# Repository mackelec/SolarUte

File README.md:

# SolarUte

The story about converting a 2000 4WD Ford Couier Diesel Ute (Mazda B2500) to Battery Electric.

## [The Story](https://github.com/mackelec/SolarUte/blob/master/The_Story/readme.md)

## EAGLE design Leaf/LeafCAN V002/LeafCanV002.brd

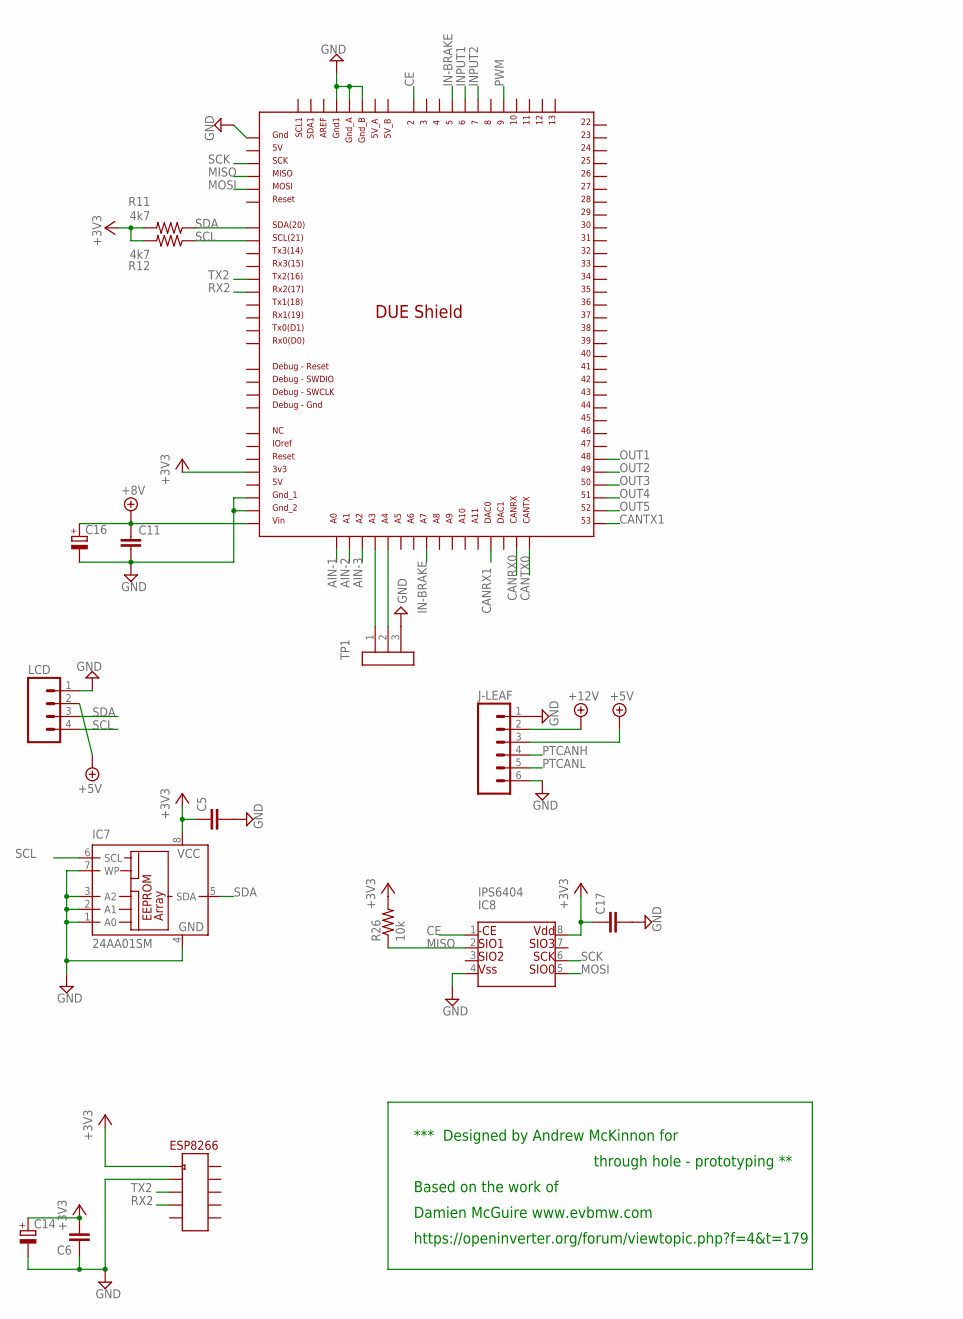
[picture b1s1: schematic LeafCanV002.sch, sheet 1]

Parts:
C5, C6, C11, C17: BCAP
C14, C16: C-RB200100; CPOL-RADIAL-10UF-25V
ESP8266: IDC10; IDC10-SMALL
IC1: DUE(NORMAL)
IC7: 24AA01SM; SO-08M
IC8: IPS6404; SO-08
J-LEAF: MO6POL; MOLEX-6
LCD: MO4POL; MOLEX-4
R11, R12: 4k7; AXIAL-0.4
R26: 10k; R1206
TP1: SIL3

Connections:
+3V3: C5.1, C6.2, C14.1 (+), C17.1, ESP8266.1, IC1.3V3, IC7.8 (VCC), IC8.8, R11.P$2 (2), R12.P$2 (2), R26.2; also elsewhere on the board
+5V: J-LEAF.3, LCD.2; also elsewhere on the board
+8V: C11.1, C16.1 (+), IC1.VIN; also elsewhere on the board
+12V: J-LEAF.2; also elsewhere on the board
AIN-1: IC1.A0; also elsewhere on the board
AIN-2: IC1.A1; also elsewhere on the board
AIN-3: IC1.A2; also elsewhere on the board
CANRX0: IC1.CANRX; also elsewhere on the board
CANRX1: IC1.DAC0; also elsewhere on the board
CANTX0: IC1.CANTX; also elsewhere on the board
CANTX1: IC1.53; also elsewhere on the board
CE: IC1.2, IC8.1
GND: C5.2, C6.1, C11.2, C14.2 (-), C16.2 (-), C17.2, ESP8266.3, IC1.5V_ICSP, IC1.GND1, IC1.GND_1, IC1.GND_2, IC1.GND_A, IC1.GND_B, IC7.1 (A0), IC7.2 (A1), IC7.3 (A2), IC7.4 (GND), IC7.7 (WP), IC8.4, J-LEAF.1, J-LEAF.6, LCD.1, TP1.3; also elsewhere on the board
IN-BRAKE: IC1.5, IC1.A7; also elsewhere on the board
INPUT1: IC1.6; also elsewhere on the board
INPUT2: IC1.7; also elsewhere on the board
MISO: IC1.MISO_ICSP, IC8.2, R26.1
MOSI: IC1.MOSI_ICSP, IC8.5
unnamed: IC1.A3, TP1.1
unnamed: IC1.A4, TP1.2
OUT1: IC1.48; also elsewhere on the board
OUT2: IC1.49; also elsewhere on the board
OUT3: IC1.50; also elsewhere on the board
OUT4: IC1.51; also elsewhere on the board
OUT5: IC1.52; also elsewhere on the board
PTCANH: J-LEAF.4; also elsewhere on the board
PTCANL: J-LEAF.5; also elsewhere on the board
PWM: IC1.9; also elsewhere on the board
RX2: ESP8266.7, IC1.RX2
SCK: IC1.SCK_ICSP, IC8.6
SCL: IC1.SCL, IC7.6 (SCL), LCD.4, R12.P$1 (1)
SDA: IC1.SDA, IC7.5 (SDA), LCD.3, R11.P$1 (1)
TX2: ESP8266.5, IC1.TX2

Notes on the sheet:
Based on the work of
Damien McGuire www.evbmw.com
https://openinverter.org/forum/viewtopic.php?f=4&t=179
*** Designed by Andrew McKinnon for
through hole - prototyping **

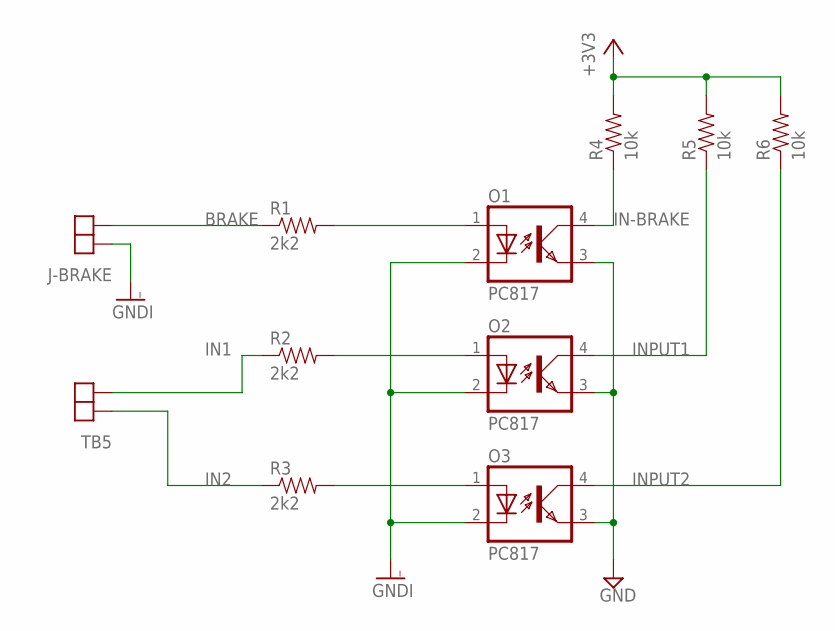
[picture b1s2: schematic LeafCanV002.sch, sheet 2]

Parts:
J-BRAKE: TB2381; TB-KF2EDG381-2P
O1, O2, O3: PC817; DIL04
R1, R2, R3: 2k2; AXIAL-0.4
R4, R5, R6: 10k; AXIAL-0.4
TB5: TB2381; TB-KF2EDG381-2P

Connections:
+3V3: R4.P$2 (2), R5.P$2 (2), R6.P$2 (2); also elsewhere on the board
BRAKE: J-BRAKE.1, R1.P$1 (1)
GND: O1.3 (EMIT), O2.3 (EMIT), O3.3 (EMIT); also elsewhere on the board
GNDI: J-BRAKE.2, O1.2 (C), O2.2 (C), O3.2 (C); also elsewhere on the board
IN1: R2.P$1 (1), TB5.1
IN2: R3.P$1 (1), TB5.2
IN-BRAKE: O1.4 (COL), R4.P$1 (1); also elsewhere on the board
INPUT1: O2.4 (COL), R5.P$1 (1); also elsewhere on the board
INPUT2: O3.4 (COL), R6.P$1 (1); also elsewhere on the board
unnamed: O3.1 (A), R3.P$2 (2)
unnamed: O2.1 (A), R2.P$2 (2)
unnamed: O1.1 (A), R1.P$2 (2)

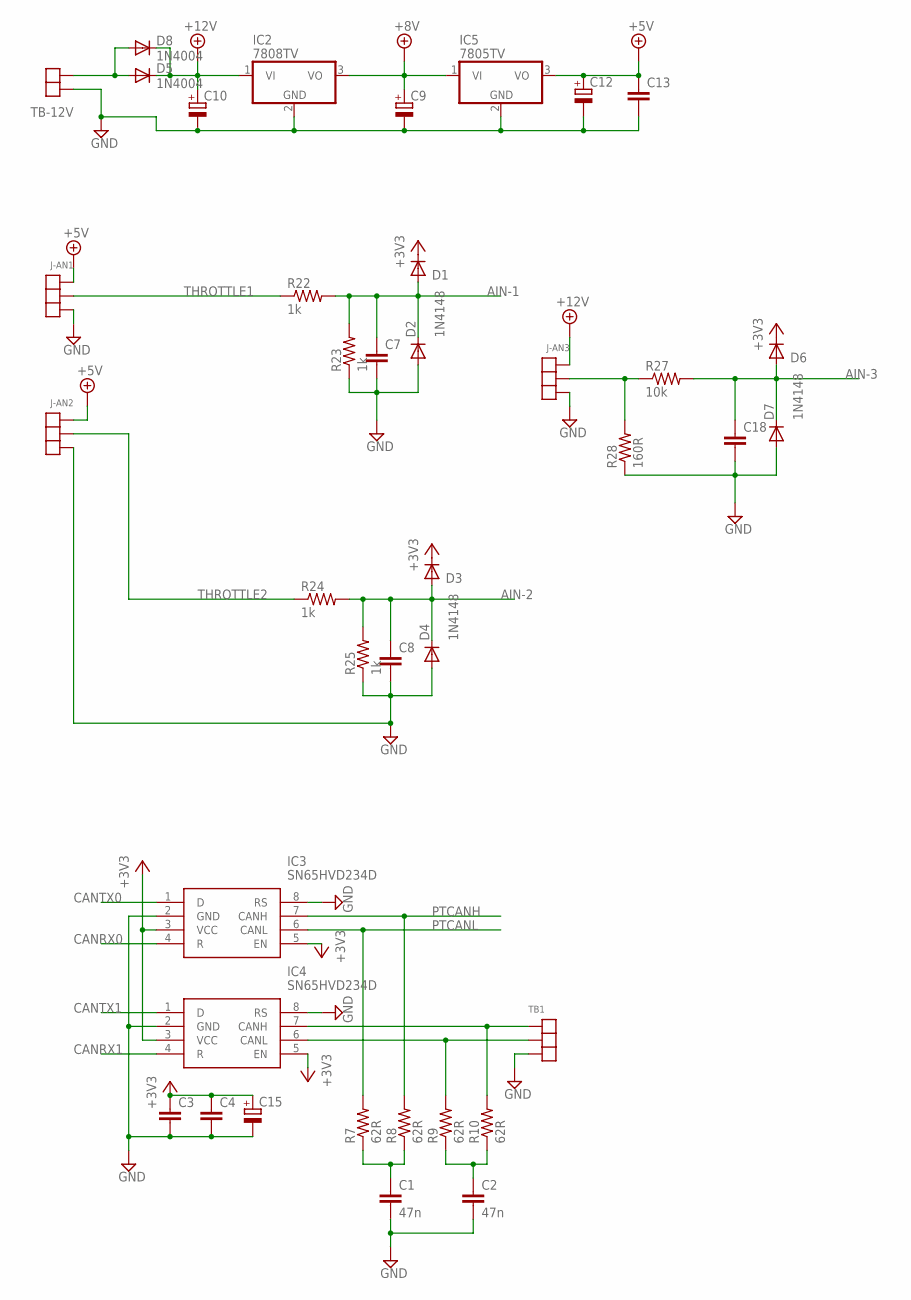
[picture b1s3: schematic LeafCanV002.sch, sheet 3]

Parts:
C1, C2: 47n; C025-030X050
C3, C4, C7, C8, C13, C18: BCAP
C9, C12, C15: C-RB200100; CPOL-RADIAL-10UF-25V
C10: CPOL-EUE7.5-18; E7,5-18
D1, D2, D3, D4, D6, D7: 1N4148; D3
D5, D8: 1N4004; DO41-10
IC2: 7808TV; TO220V
IC3, IC4: SN65HVD234D; SOIC127P600X175-8N
IC5: 7805TV; TO220V
J-AN1, J-AN2, J-AN3: TB3381V; TB-KF2EDG381-3-V
R7, R8, R9, R10: 62R; AXIAL-0.4
R22, R23, R24, R25: 1k; AXIAL-0.4
R27: 10k; AXIAL-0.4
R28: 160R; AXIAL-0.4
TB1: TB3381V; TB-KF2EDG381-3-V
TB-12V: TB2381; TB-KF2EDG381-2P

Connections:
+3V3: C3.1, C4.1, C15.1 (+), D1.C, D3.C, D6.C, IC3.3 (VCC), IC3.5 (EN), IC4.3 (VCC), IC4.5 (EN); also elsewhere on the board
+5V: C12.1 (+), C13.1, IC5.3 (VO), J-AN1.1, J-AN2.1; also elsewhere on the board
+8V: C9.1 (+), IC2.3 (VO), IC5.1 (VI); also elsewhere on the board
+12V: C10.+, D5.C, D8.C, IC2.1 (VI), J-AN3.1; also elsewhere on the board
AIN-1: C7.1, D1.A, D2.C, R22.P$2 (2), R23.P$2 (2); also elsewhere on the board
AIN-2: C8.1, D3.A, D4.C, R24.P$2 (2), R25.P$2 (2); also elsewhere on the board
AIN-3: C18.1, D6.A, D7.C, R27.P$2 (2); also elsewhere on the board
CANRX0: IC3.4 (R); also elsewhere on the board
CANRX1: IC4.4 (R); also elsewhere on the board
CANTX0: IC3.1 (D); also elsewhere on the board
CANTX1: IC4.1 (D); also elsewhere on the board
GND: C1.2, C2.2, C3.2, C4.2, C7.2, C8.2, C9.2 (-), C10.-, C12.2 (-), C13.2, C15.2 (-), C18.2, D2.A, D4.A, D7.A, IC2.2 (GND), IC3.2 (GND), IC3.8 (RS), IC4.2 (GND), IC4.8 (RS), IC5.2 (GND), J-AN1.3, J-AN2.3, J-AN3.3, R23.P$1 (1), R25.P$1 (1), R28.P$1 (1), TB1.3, TB-12V.2; also elsewhere on the board
unnamed: C1.1, R7.P$1 (1), R8.P$1 (1)
unnamed: C2.1, R9.P$1 (1), R10.P$1 (1)
unnamed: J-AN3.2, R27.P$1 (1), R28.P$2 (2)
unnamed: IC4.7 (CANH), R10.P$2 (2), TB1.1
unnamed: IC4.6 (CANL), R9.P$2 (2), TB1.2
unnamed: D5.A, D8.A, TB-12V.1
PTCANH: IC3.7 (CANH), R8.P$2 (2); also elsewhere on the board
PTCANL: IC3.6 (CANL), R7.P$2 (2); also elsewhere on the board
THROTTLE1: J-AN1.2, R22.P$1 (1)
THROTTLE2: J-AN2.2, R24.P$1 (1)

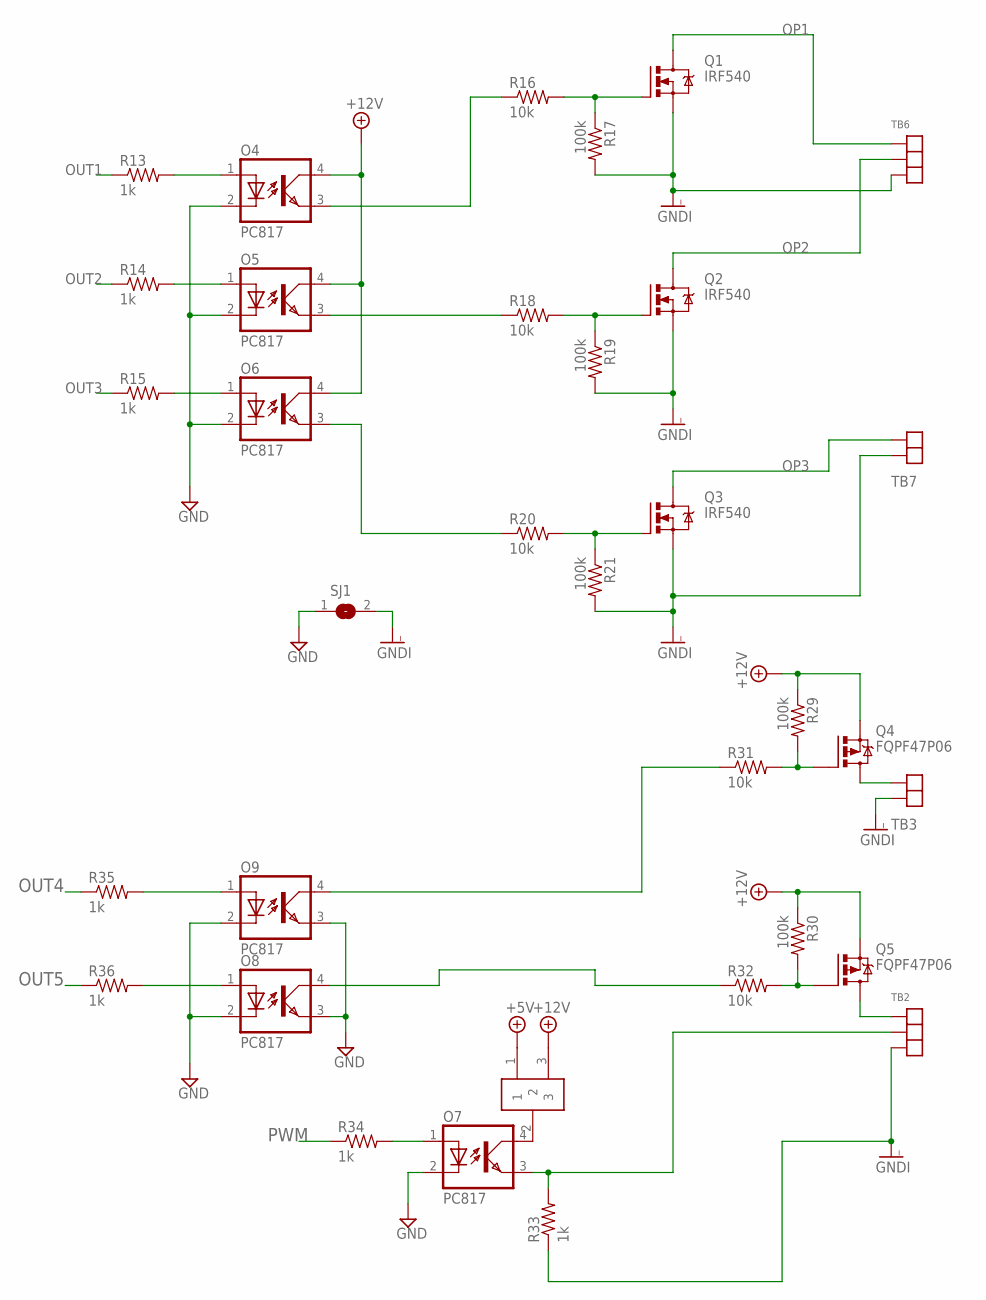
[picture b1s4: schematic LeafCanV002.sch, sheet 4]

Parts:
JP1: JP1X3
O4, O5, O6, O7: PC817; DIL04
O8, O9: PC817; DIL04; MPN PC817X4J000F
Q1, Q2, Q3: IRF540; TO220BV
Q4, Q5: FQPF47P06; TO220BV
R13, R14, R15, R33, R34, R35, R36: 1k; AXIAL-0.4
R16, R18, R20, R31, R32: 10k; AXIAL-0.4
R17, R19, R21, R29, R30: 100k; AXIAL-0.4
SJ1: SJ
TB2, TB6: TB3381; TB-KF2EDG381-3P
TB3, TB7: TB2381; TB-KF2EDG381-2P

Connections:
+5V: JP1.1; also elsewhere on the board
+12V: JP1.3, O4.4 (COL), O5.4 (COL), O6.4 (COL), Q4.S, Q5.S, R29.P$1 (1), R30.P$1 (1); also elsewhere on the board
G-DCCONV: O8.4 (COL), R32.P$1 (1)
GND: O4.2 (C), O5.2 (C), O6.2 (C), O7.2 (C), O8.2 (C), O8.3 (EMIT), O9.2 (C), O9.3 (EMIT), SJ1.1; also elsewhere on the board
GNDI: Q1.S, Q2.S, Q3.S, R17.P$2 (2), R19.P$2 (2), R21.P$2 (2), R33.P$1 (1), SJ1.2, TB2.3, TB3.2, TB6.3, TB7.2; also elsewhere on the board
unnamed: Q1.G, R16.P$2 (2), R17.P$1 (1)
unnamed: Q2.G, R18.P$2 (2), R19.P$1 (1)
unnamed: Q3.G, R20.P$2 (2), R21.P$1 (1)
unnamed: O4.1 (A), R13.P$2 (2)
unnamed: O5.1 (A), R14.P$2 (2)
unnamed: O6.1 (A), R15.P$2 (2)
unnamed: O6.3 (EMIT), R20.P$1 (1)
unnamed: O5.3 (EMIT), R18.P$1 (1)
unnamed: O4.3 (EMIT), R16.P$1 (1)
unnamed: Q4.D, TB3.1
unnamed: O7.3 (EMIT), R33.P$2 (2), TB2.2
unnamed: JP1.2, O7.4 (COL)
unnamed: O7.1 (A), R34.P$2 (2)
unnamed: Q5.G, R30.P$2 (2), R32.P$2 (2)
unnamed: Q4.G, R29.P$2 (2), R31.P$2 (2)
unnamed: Q5.D, TB2.1
unnamed: O9.4 (COL), R31.P$1 (1)
unnamed: O8.1 (A), R36.P$2 (2)
unnamed: O9.1 (A), R35.P$2 (2)
OP1: Q1.D, TB6.1
OP2: Q2.D, TB6.2
OP3: Q3.D, TB7.1
OUT1: R13.P$1 (1); also elsewhere on the board
OUT2: R14.P$1 (1); also elsewhere on the board
OUT3: R15.P$1 (1); also elsewhere on the board
OUT4: R35.P$1 (1); also elsewhere on the board
OUT5: R36.P$1 (1); also elsewhere on the board
PWM: R34.P$1 (1); also elsewhere on the board

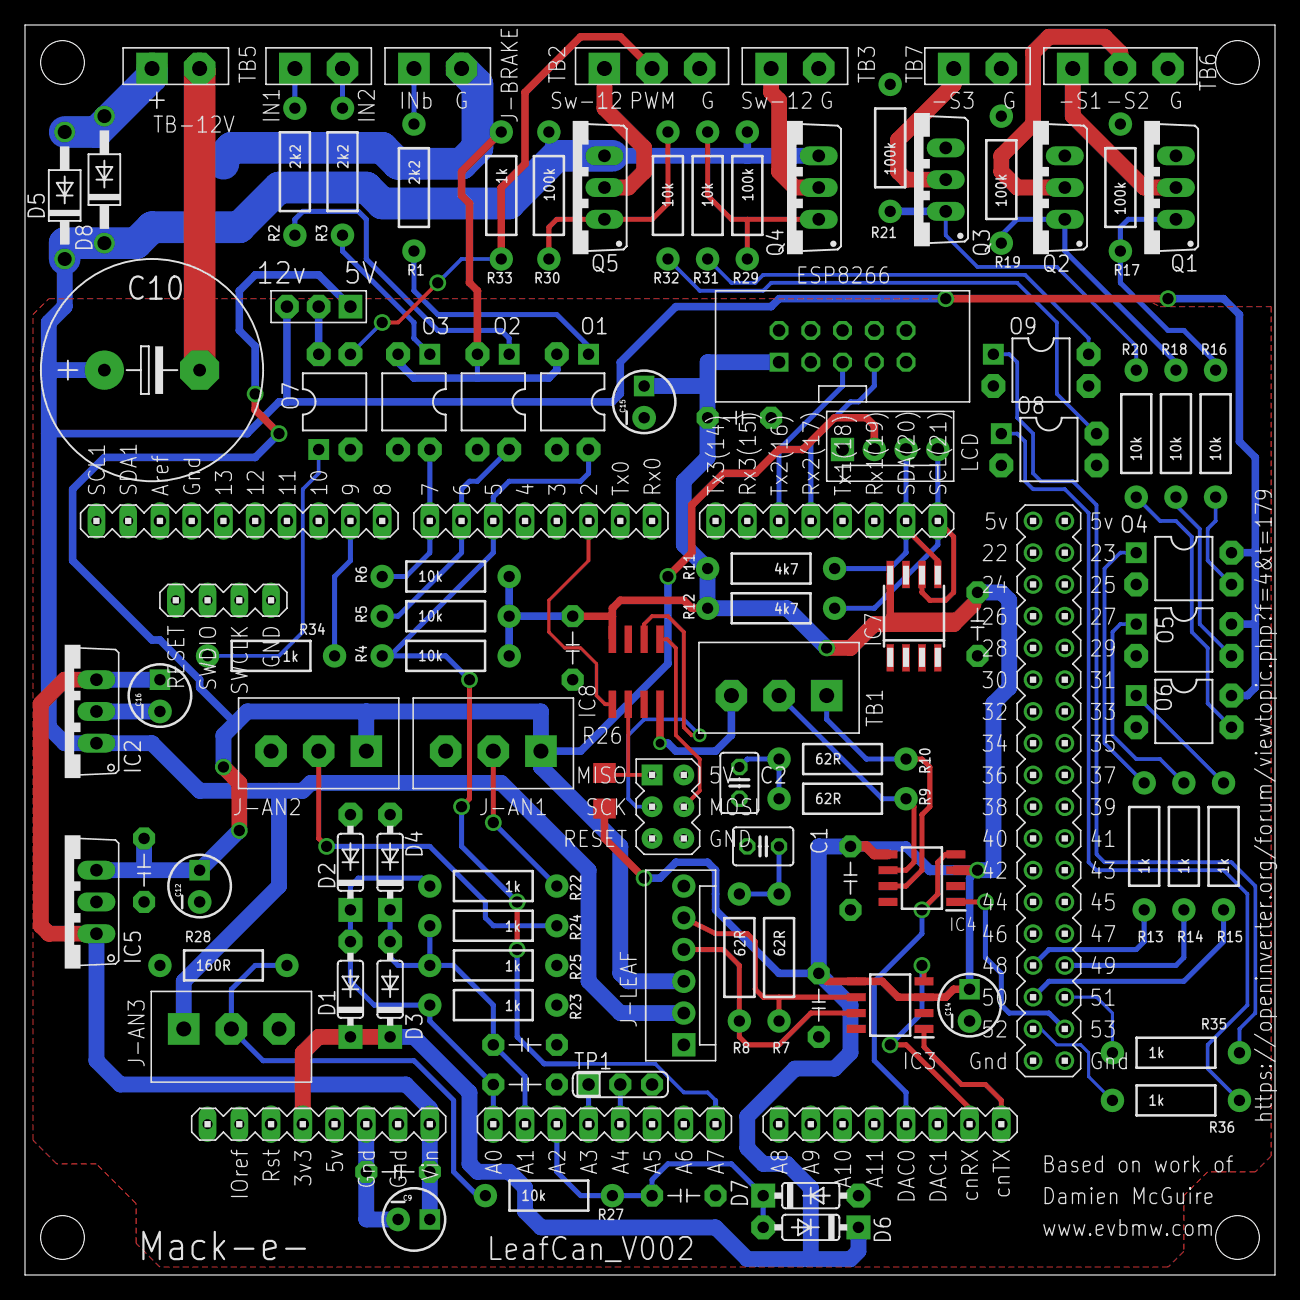
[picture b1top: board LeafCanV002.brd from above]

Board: 2 copper layers, 100.0 x 100.0 mm, 100 parts (1 on the bottom side), 71 nets.

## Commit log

2020-07-24 Create notes
